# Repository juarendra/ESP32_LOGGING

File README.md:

# ESP32_LOGGING

## Table of Content

* [Product Specsification](#product-specsification)
* [Technical Spesification](#technical-spesification)
* [Applications](#applications)
* [Advantages](#advantages)
* [Priview Hardware](#priview-hardware)
* [Documentation](#documentation)
  * [Pinout Diagram](#pinout-diagram)
  * [Dimension](#dimension)
  * [BOM](#bom)
  * [Schematic](#schematic0)
  * [Example Program](#examples-program)
* [FAQ](#FAQ)

## Preview Hardware

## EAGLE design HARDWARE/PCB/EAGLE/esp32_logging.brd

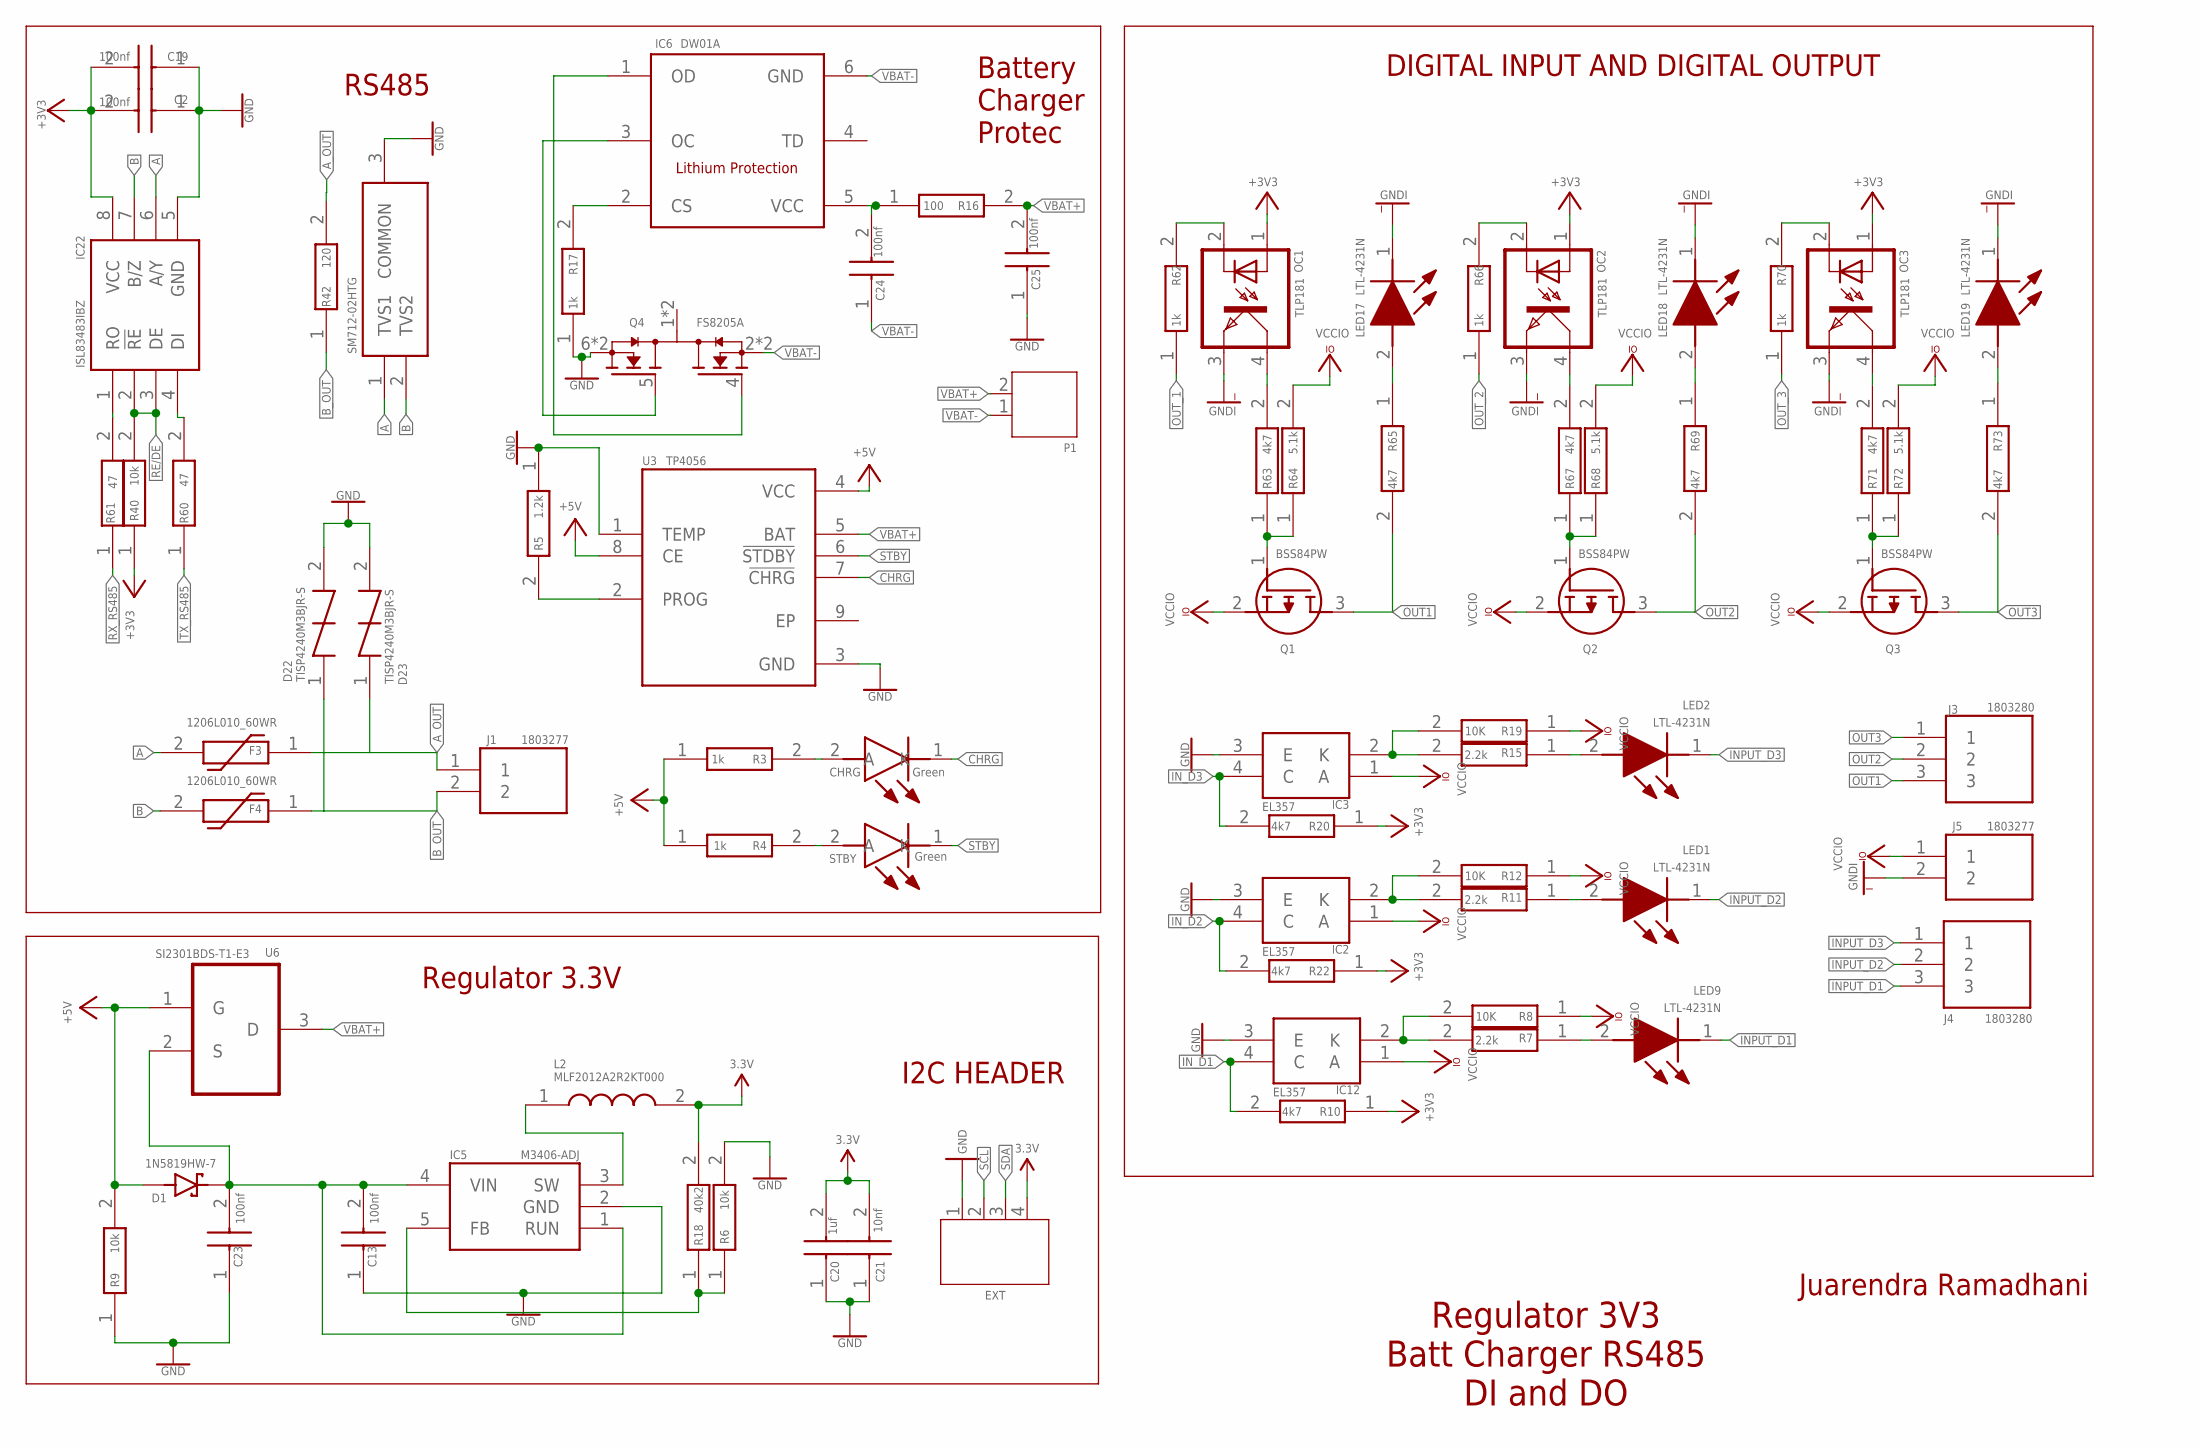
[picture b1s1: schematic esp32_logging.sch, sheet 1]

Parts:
C2, C13, C19, C23, C24, C25: 100nf; CAPC1608X87N
C20: 1uf; CAPC1608X87N
C21: 10nf; CAPC1608X87N
CHRG: Green; LEDC2012X80N
D1: 1N5819HW-7; SOD3715X145N
D6: SM712-02HTG; SOT95P237X111-3N
D22, D23: TISP4240M3BJR-S; TISP4240M3BJRS
EXT: JST-PH4
F3, F4: 1206L010_60WR; 1206L075132WR
IC2, IC3, IC12: EL357
IC5: M3406-ADJ; SOT95P280X100-5N
IC6: DW01A; SOT23-6
IC22: ISL83483IBZ; SOIC127P600X175-8N
J1, J5: 1803277
J3, J4: 1803280
L2: MLF2012A2R2KT000; INDC2012X105N
LED1, LED2, LED9, LED17, LED18, LED19: LTL-4231N; LTL4231N
OC1, OC2, OC3: TLP181; SO-4
P1: JST-PH2
Q1, Q2, Q3: BSS84PW; SOT65P210X100-3N
Q4: FS8205A; SOP65P640X120-8N
R3, R4, R17, R62, R66, R70: 1k; RESC1608X55N
R5: 1.2k; RESC1608X55N
R6, R9, R40: 10k; RESC1608X55N
R7, R11, R15: 2.2k; RESC2012X60N
R8, R12, R19: 10K; RESC1608X55N
R10, R20, R22, R63, R65, R67, R69, R71, R73: 4k7; ERA3AEB101V
R16: 100; RESC1608X55N
R18: 40k2; RESC1608X55N
R42: 120; RESC2012X65N
R60, R61: 47; RESC1608X55N
R64, R68, R72: 5.1k; RESC1608X55N
STBY: Green; LEDC2012X80N
U3: TP4056; SOP127P600X175-9N
U6: SI2301BDS-T1-E3; SOT95P237X112-3N

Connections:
3.3V: C2.2, C19.2, C20.2, C21.2, EXT.4, IC22.8 (VCC), L2.2, OC1.1 (A), OC2.1 (A), OC3.1 (A), R10.1, R18.2, R20.1, R22.1, R40.1; also elsewhere on the board
+5V: D1.A, R3.1, R4.1, R9.2, U3.4 (VCC), U3.8 (CE), U6.1 (G); also elsewhere on the board
A: D6.1 (TVS1), F3.2, IC22.6 (A/Y)
A_OUT: D23.1, F3.1, J1.1, R42.2
B: D6.2 (TVS2), F4.2, IC22.7 (B/Z)
B_OUT: D22.1, F4.1, J1.2, R42.1
CHRG: CHRG.1 (K), U3.7 (!CHRG)
GND: C2.1, C13.1, C19.1, C20.1, C21.1, C23.1, C25.1, D6.3 (COMMON), D22.2, D23.2, EXT.1, IC2.3 (E), IC3.3 (E), IC5.2 (GND), IC12.3 (E), IC22.5 (GND), Q4.6 (S2), Q4.7 (S2), R5.1, R6.2, R9.1, R17.1, U3.1 (TEMP), U3.3 (GND); also elsewhere on the board
GNDI: J5.2, LED17.1 (K), LED18.1 (K), LED19.1 (K), OC1.3 (EMIT), OC2.3 (EMIT), OC3.3 (EMIT)
INPUT_D1: J4.3, LED9.1 (K)
INPUT_D2: J4.2, LED1.1 (K)
INPUT_D3: J4.1, LED2.1 (K)
IN_D1: IC12.4 (C), R10.2; also elsewhere on the board
IN_D2: IC2.4 (C), R22.2; also elsewhere on the board
IN_D3: IC3.4 (C), R20.2; also elsewhere on the board
unnamed: C13.2, C23.2, D1.C (K), IC5.1 (RUN), IC5.4 (VIN), U6.2 (S)
unnamed: C24.2, IC6.5 (VCC), R16.1
unnamed: R4.2, STBY.2 (A)
unnamed: R5.2, U3.2 (PROG)
unnamed: IC6.1 (OD), Q4.4 (G1)
unnamed: IC5.3 (SW), L2.1
unnamed: IC2.2 (K), R11.2, R12.2
unnamed: IC12.2 (K), R7.2, R8.2
unnamed: CHRG.2 (A), R3.2
unnamed: LED1.2 (A), R11.1
unnamed: IC3.2 (K), R15.2, R19.2
unnamed: LED2.2 (A), R15.1
unnamed: OC1.4 (COL), R63.2
unnamed: IC6.2 (CS), R17.2
unnamed: IC5.5 (FB), R6.1, R18.1
unnamed: IC6.3 (OC), Q4.5 (G2)
unnamed: OC1.2 (C), R62.2
unnamed: Q1.1 (G), R63.1, R64.1
unnamed: OC2.4 (COL), R67.2
unnamed: LED17.2 (A), R65.1
unnamed: OC2.2 (C), R66.2
unnamed: Q2.1 (G), R67.1, R68.1
unnamed: LED18.2 (A), R69.1
unnamed: OC3.4 (COL), R71.2
unnamed: OC3.2 (C), R70.2
unnamed: Q3.1 (G), R71.1, R72.1
unnamed: LED19.2 (A), R73.1
unnamed: IC22.1 (RO), R61.2
unnamed: IC22.4 (DI), R60.2
unnamed: LED9.2 (A), R7.1
OUT1: J3.3, Q1.3 (D), R65.2
OUT2: J3.2, Q2.3 (D), R69.2
OUT3: J3.1, Q3.3 (D), R73.2
OUT_1: R62.1; also elsewhere on the board
OUT_2: R66.1; also elsewhere on the board
OUT_3: R70.1; also elsewhere on the board
RE/DE: IC22.2 (!RE), IC22.3 (DE), R40.2
RX_RS485: R61.1; also elsewhere on the board
SCL: EXT.2; also elsewhere on the board
SDA: EXT.3; also elsewhere on the board
STBY: STBY.1 (K), U3.6 (!STDBY)
TX_RS485: R60.1; also elsewhere on the board
VBAT+: C25.2, P1.2, R16.2, U3.5 (BAT), U6.3 (D)
VBAT-: C24.1, IC6.6 (GND), P1.1, Q4.2 (S1), Q4.3 (S1)
VCCIO: IC2.1 (A), IC3.1 (A), IC12.1 (A), J5.1, Q1.2 (S), Q2.2 (S), Q3.2 (S), R8.1, R12.1, R19.1, R64.2, R68.2, R72.2

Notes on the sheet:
Battery Charger Protec
Regulator 3.3V
I2C HEADER
Regulator 3V3 Batt Charger RS485 DI and DO
DIGITAL INPUT AND DIGITAL OUTPUT
Juarendra Ramadhani
RS485

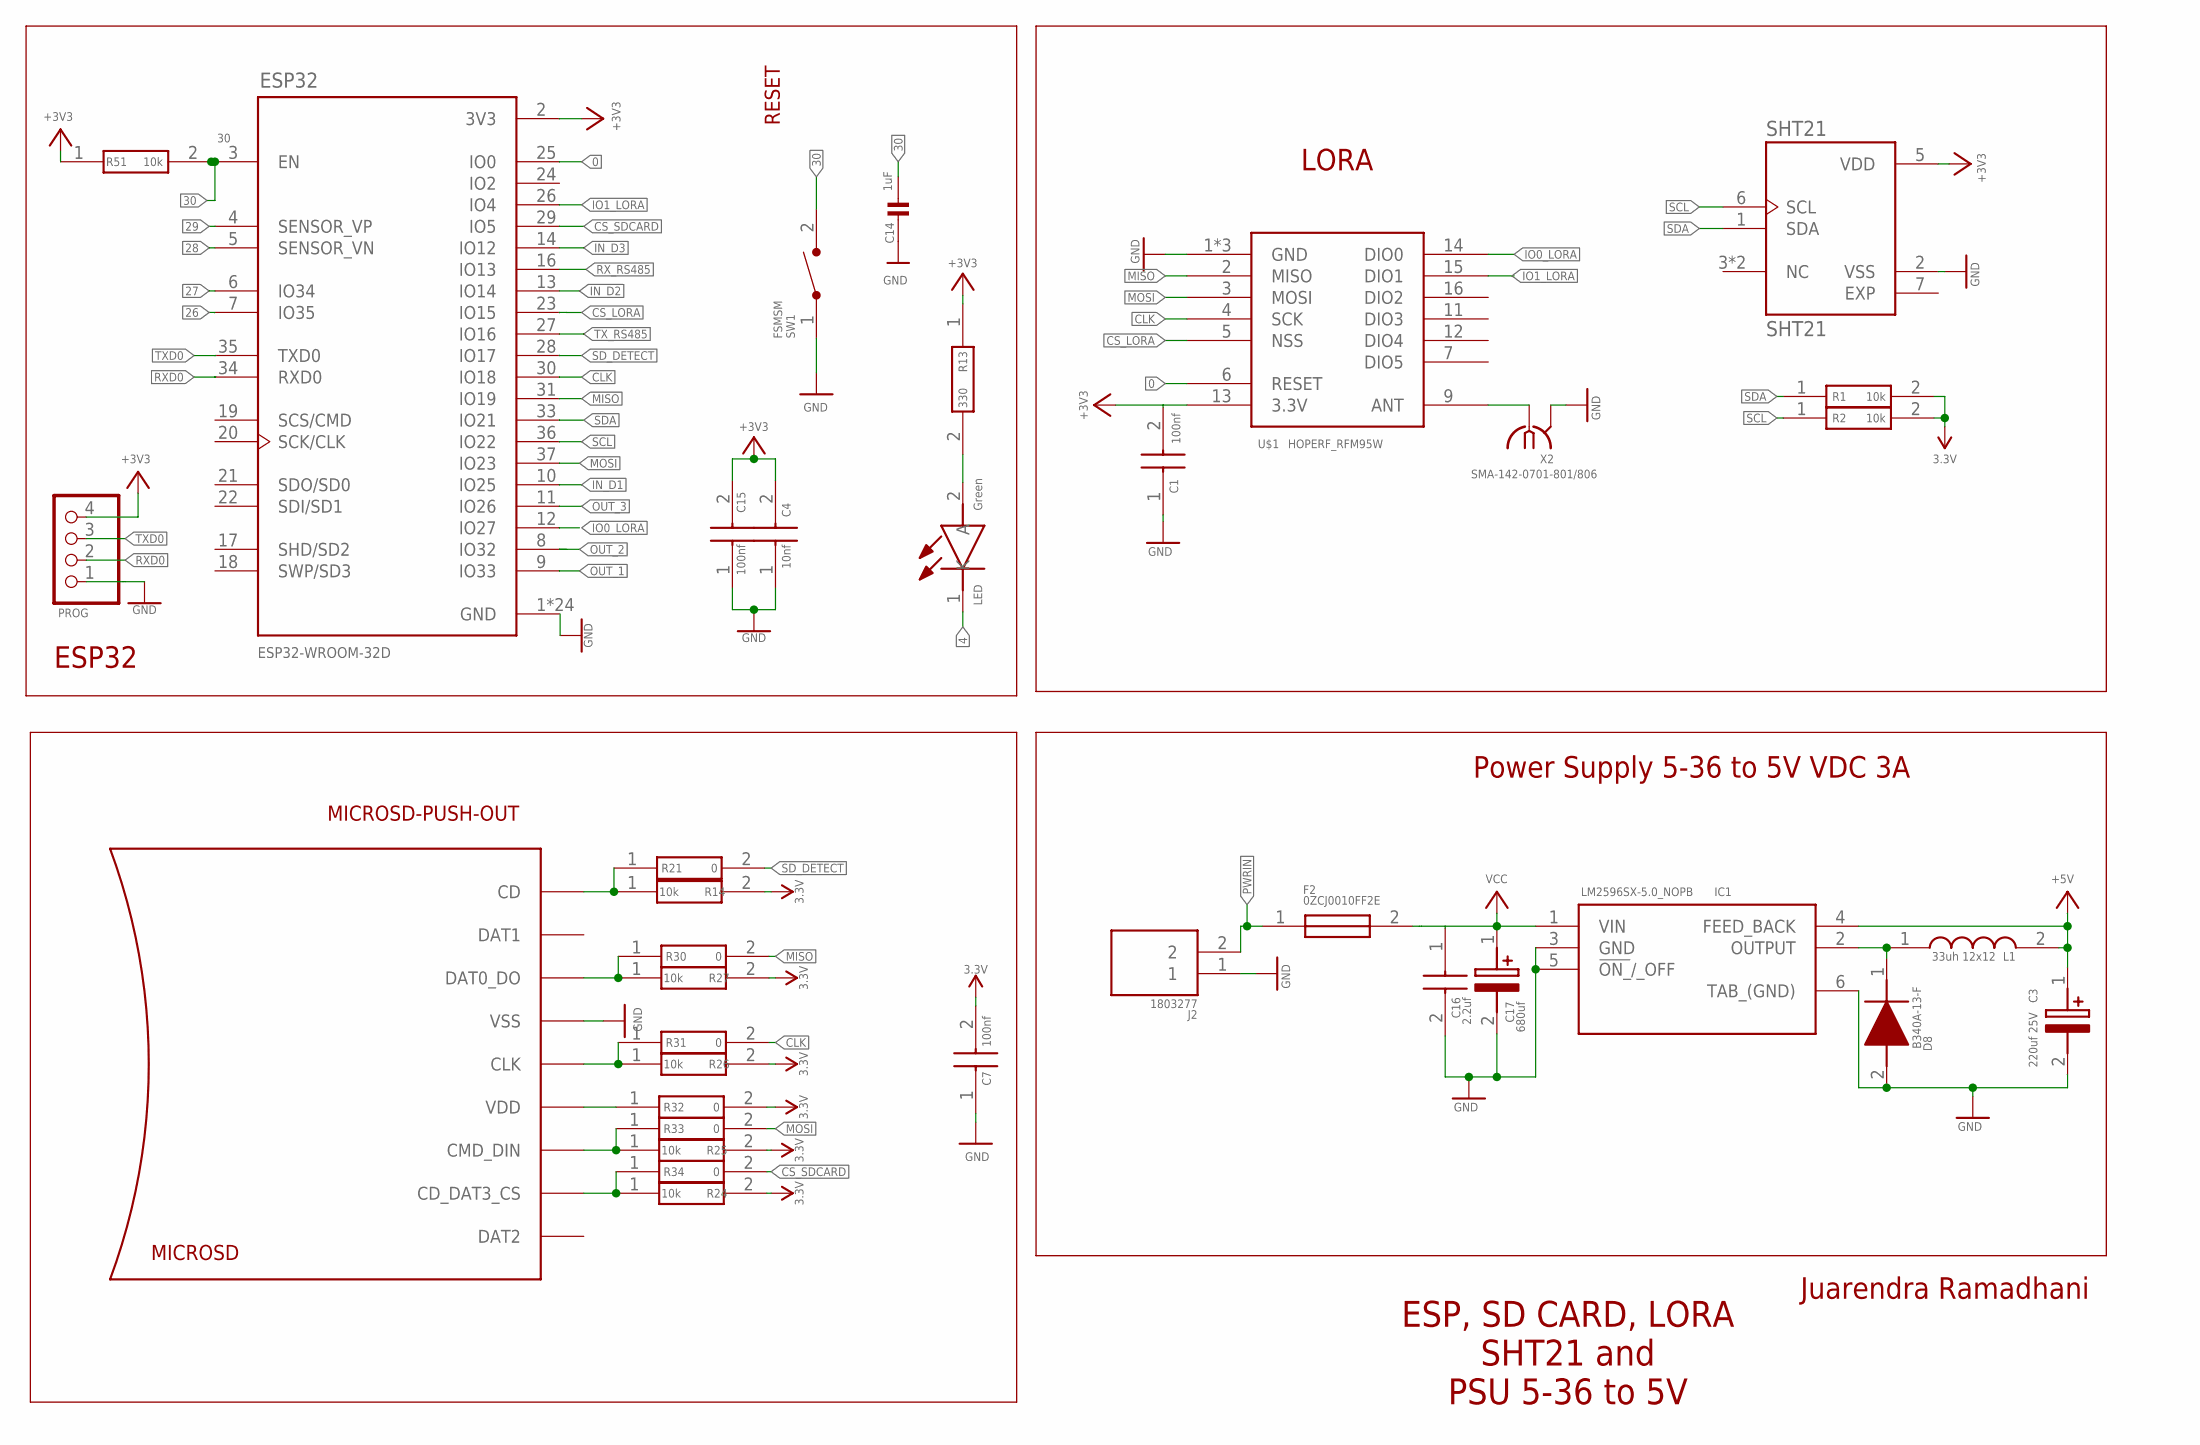
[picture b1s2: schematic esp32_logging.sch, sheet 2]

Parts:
C1, C7, C15: 100nf; CAPC1608X87N
C3: 220uf 25V; CAPPRD350W60D850H1250
C4: 10nf; CAPC1608X87N
C14: 1uF; 0603
C16: 2.2uf; CAPC2012X140N
C17: 680uf; EEHZS1H221P
D8: B340A-13-F; DIOM5226X240N
ESP32: ESP32-WROOM-32D; MODULE_ESP32-WROOM-32D
F2: 0ZCJ0010FF2E; FUSC3216X75N
IC1: LM2596SX-5.0_NOPB; KTT0005B
J2: 1803277
L1: 33uh 12x12; WE-PD_1260/1245/1280/121054
LED: Green; LEDC2012X80N
MICROSD: MICROSD-PUSH-OUT
PROG: PINHD-1X4; 1X04
R1, R2, R14, R24, R25, R26, R27, R51: 10k; RESC1608X55N
R13: 330; ERJH3
R21, R30, R31, R32, R33, R34: 0; RESC1608X55N
SHT21: SHT21; XDCR_SHT21
SW1: FSMSM
U$1: HOPERF_RFM95W
X2: SMA-142-0701-801/806; J502-ND-142-0701-801/806

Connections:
0: ESP32.25 (IO0), U$1.6 (RESET)
3.3V: C1.2, C4.2, C7.2, C15.2, ESP32.2 (3V3), PROG.4, R1.2, R2.2, R13.1, R14.2, R24.2, R25.2, R26.2, R27.2, R32.2, R51.1, SHT21.5 (VDD), U$1.13 (3.3V); also elsewhere on the board
4: LED.1 (K)
26: ESP32.7 (IO35)
27: ESP32.6 (IO34)
28: ESP32.5 (SENSOR_VN)
29: ESP32.4 (SENSOR_VP)
30: C14.1, ESP32.3 (EN), R51.2, SW1.2
+5V: C3.1 (+), IC1.4 (FEED_BACK), L1.2; also elsewhere on the board
CLK: ESP32.30 (IO18), R31.2, U$1.4 (SCK)
CS_LORA: ESP32.23 (IO15), U$1.5 (NSS)
CS_SDCARD: ESP32.29 (IO5), R34.2
GND: C1.1, C3.2 (-), C4.1, C7.1, C14.2, C15.1, C16.2, C17.2 (-), D8.2 (A), ESP32.1 (GND), ESP32.15 (GND), ESP32.38 (GND), ESP32.39_1 (GND), ESP32.39_2 (GND), ESP32.39_3 (GND), ESP32.39_4 (GND), ESP32.39_5 (GND), ESP32.39_6 (GND), ESP32.39_7 (GND), ESP32.39_8 (GND), ESP32.39_9 (GND), ESP32.39_10 (GND), ESP32.39_11 (GND), ESP32.39_12 (GND), ESP32.39_13 (GND), ESP32.39_14 (GND), ESP32.39_15 (GND), ESP32.39_16 (GND), ESP32.39_17 (GND), ESP32.39_18 (GND), ESP32.39_19 (GND), ESP32.39_20 (GND), ESP32.39_21 (GND), IC1.3 (GND), IC1.5 (!ON_!/_OFF), IC1.6 (TAB_(GND)), J2.1, MICROSD.6 (VSS), MICROSD.G1 (VSS), MICROSD.G2 (VSS), MICROSD.G3 (VSS), MICROSD.G4 (VSS), PROG.1, SHT21.2 (VSS), SW1.1, U$1.1 (GND), U$1.8 (GND), U$1.10 (GND), X2.G@1 (2), X2.G@2 (2), X2.G@3 (2), X2.G@4 (2); also elsewhere on the board
IN_D1: ESP32.10 (IO25); also elsewhere on the board
IN_D2: ESP32.13 (IO14); also elsewhere on the board
IN_D3: ESP32.14 (IO12); also elsewhere on the board
IO0_LORA: ESP32.12 (IO27), U$1.14 (DIO0)
IO1_LORA: ESP32.26 (IO4), U$1.15 (DIO1)
MISO: ESP32.31 (IO19), R30.2, U$1.2 (MISO)
MOSI: ESP32.37 (IO23), R33.2, U$1.3 (MOSI)
unnamed: MICROSD.CD, R14.1, R21.1
unnamed: MICROSD.7 (DAT0_DO), R27.1, R30.1
unnamed: U$1.9 (ANT), X2.1
unnamed: MICROSD.5 (CLK), R26.1, R31.1
unnamed: MICROSD.3 (CMD_DIN), R25.1, R33.1
unnamed: MICROSD.2 (CD_DAT3_CS), R24.1, R34.1
unnamed: D8.1 (K), IC1.2 (OUTPUT), L1.1
unnamed: MICROSD.4 (VDD), R32.1
unnamed: LED.2 (A), R13.2
OUT_1: ESP32.9 (IO33); also elsewhere on the board
OUT_2: ESP32.8 (IO32); also elsewhere on the board
OUT_3: ESP32.11 (IO26); also elsewhere on the board
PWRIN: F2.1, J2.2
RXD0: ESP32.34 (RXD0), PROG.2
RX_RS485: ESP32.16 (IO13); also elsewhere on the board
SCL: ESP32.36 (IO22), R2.1, SHT21.6 (SCL); also elsewhere on the board
SDA: ESP32.33 (IO21), R1.1, SHT21.1 (SDA); also elsewhere on the board
SD_DETECT: ESP32.28 (IO17), R21.2
TXD0: ESP32.35 (TXD0), PROG.3
TX_RS485: ESP32.27 (IO16); also elsewhere on the board
VCC: C16.1, C17.1 (+), F2.2, IC1.1 (VIN)

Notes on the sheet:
RESET
ESP32
ESP, SD CARD, LORA SHT21 and PSU 5-36 to 5V
Power Supply 5-36 to 5V VDC 3A
LORA
Juarendra Ramadhani

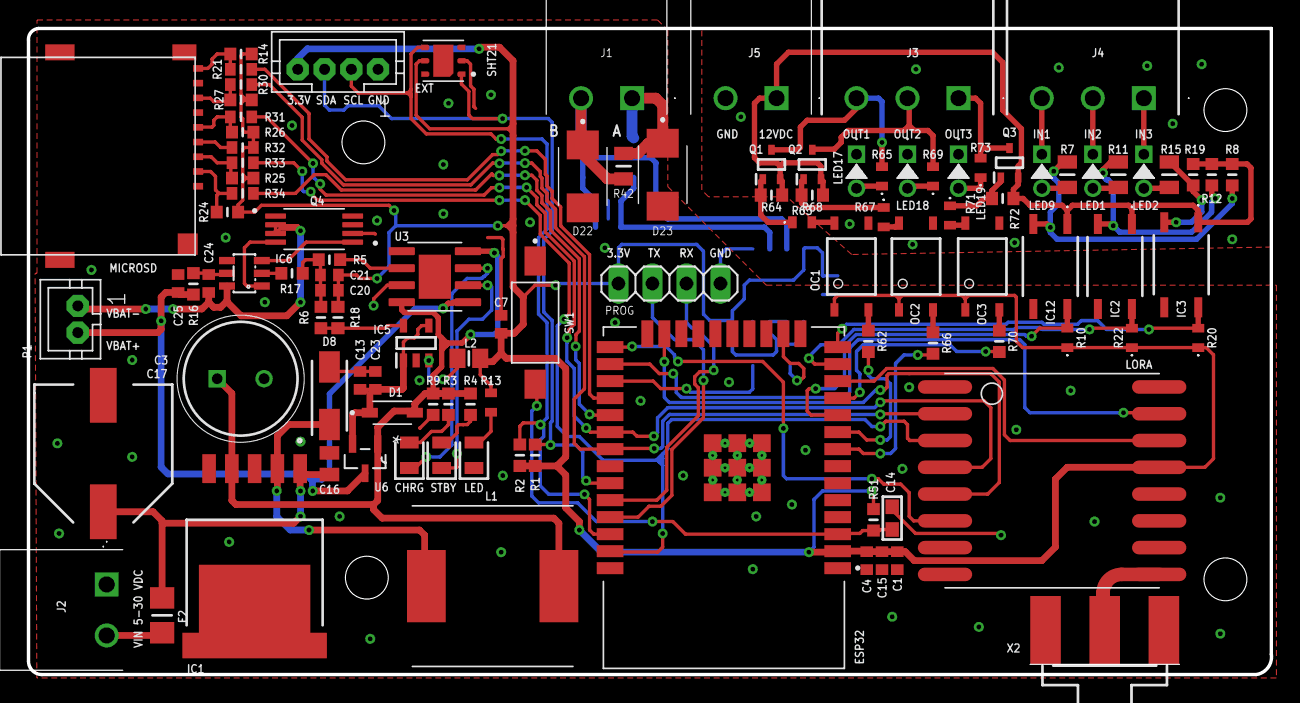
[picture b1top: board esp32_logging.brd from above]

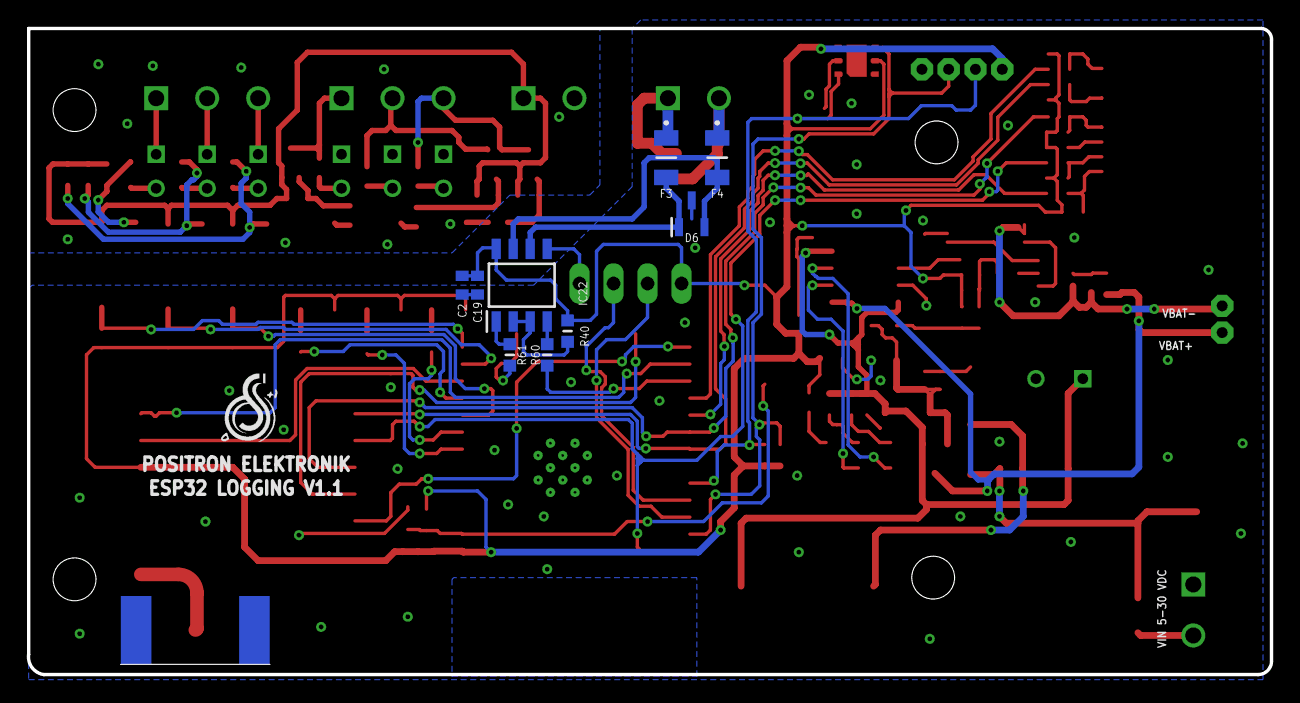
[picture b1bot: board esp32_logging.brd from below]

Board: 2 copper layers, 92.9 x 48.3 mm, 113 parts (9 on the bottom side), 83 nets.

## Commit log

2025-06-30 FEAT : add first design pcb
2025-07-01 FEAT : update pcb and documentation file
2025-07-06 FEAT: add rs485 line

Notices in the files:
parts and their libraries:
microbuilder: This work is placed in the public domain, and may be freely used for commercial and non-commercial work with the following conditions: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
